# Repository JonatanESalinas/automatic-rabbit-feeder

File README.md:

# automatic-rabbit-feeder
Files to build an atomatic rabbit feeder prototype using PIC18F4550 microcontroller, a gearmotor, and a DS3231 module.

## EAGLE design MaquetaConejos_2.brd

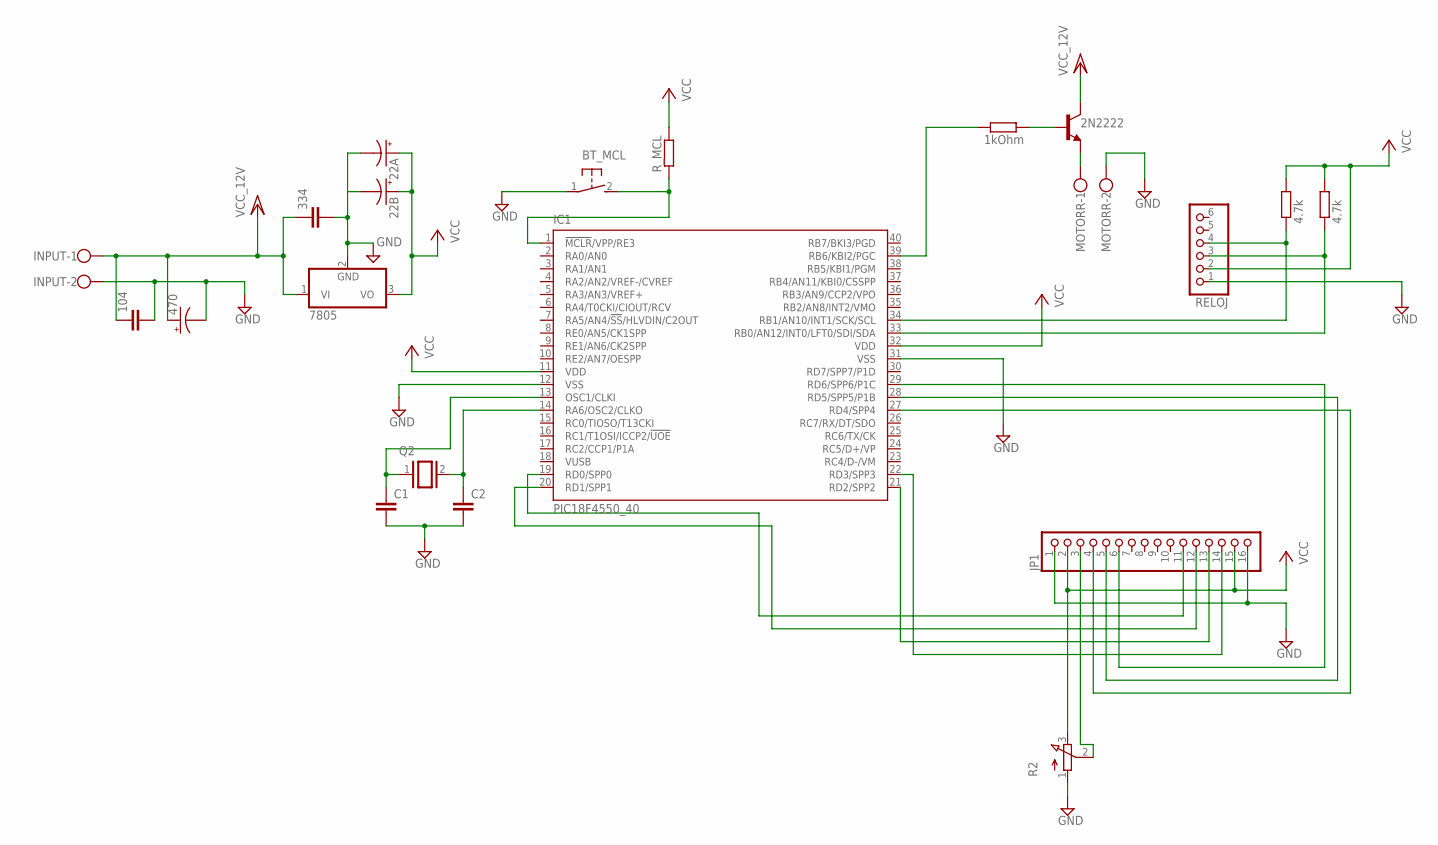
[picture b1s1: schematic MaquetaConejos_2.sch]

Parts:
22A, 22B: CPOL-USE1.8-4; E1,8-4
104, 334: C-EU050-025X075; C050-025X075
470: CPOL-USE5-10.5; E5-10,5
BT_MCL: DTS-3
C1, C2: C-EU025-024X044; C025-024X044
IC1: PIC18F4550_40; DIL40
IC3: 7805; TO220V
INPUT: W237-102
JP1: PINHD-1X16; 1X16
MOTORR: W237-102
Q2: XTAL/S; QS
R1, R4: 4.7k; 0204/7
R2: 3RP/1610N
R3: 1kOhm; 0204/7
RELOJ: PINHD-1X6; 1X06
R_MCL: R-EU_0204/7; 0204/7
T1: 2N2222; TO92-EBC-OVAL

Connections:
GND: 22A.-, 22B.-, 104.2, 334.2, 470.-, BT_MCL.1, C1.2, C2.2, IC1.12 (VSS), IC1.31 (VSS), IC3.2 (GND), INPUT.2, JP1.1, JP1.16, MOTORR.2, R2.1 (A), RELOJ.1
unnamed: BT_MCL.2, IC1.1 (!MCLR!/VPP/RE3), R_MCL.1
unnamed: IC1.39 (RB6/KBI2/PGC), R3.1
unnamed: R3.2, T1.B
unnamed: IC1.34 (RB1/AN10/INT1/SCK/SCL), R4.1, RELOJ.4
unnamed: MOTORR.1, T1.E
unnamed: C1.1, IC1.13 (OSC1/CLKI), Q2.1
unnamed: C2.1, IC1.14 (RA6/OSC2/CLKO), Q2.2
unnamed: IC1.33 (RB0/AN12/INT0/LFT0/SDI/SDA), R1.1, RELOJ.3
unnamed: JP1.3, R2.2 (S)
unnamed: IC1.19 (RD0/SPP0), JP1.11
unnamed: IC1.20 (RD1/SPP1), JP1.12
unnamed: IC1.21 (RD2/SPP2), JP1.13
unnamed: IC1.22 (RD3/SPP3), JP1.14
unnamed: IC1.27 (RD4/SPP4), JP1.4
unnamed: IC1.29 (RD6/SPP6/P1C), JP1.6
unnamed: IC1.28 (RD5/SPP5/P1B), JP1.5
VCC: 22A.+, 22B.+, IC1.11 (VDD), IC1.32 (VDD), IC3.3 (VO), JP1.2, JP1.15, R1.2, R2.3 (E), R4.2, RELOJ.2, R_MCL.2
VCC/2: 104.1, 334.1, 470.+, IC3.1 (VI), INPUT.1, T1.C

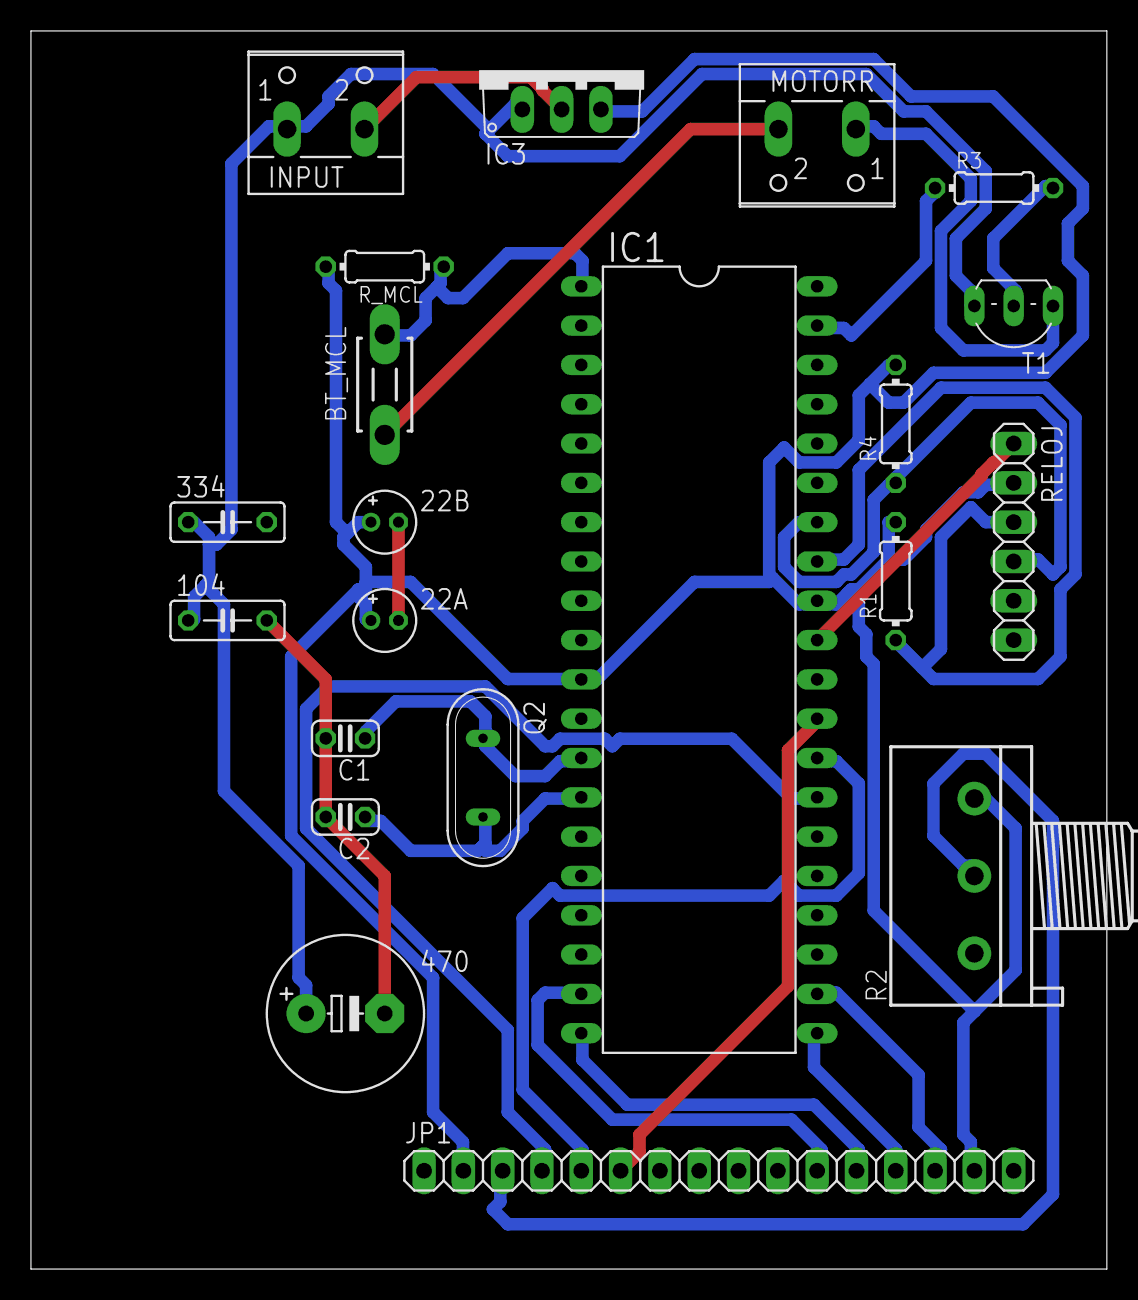
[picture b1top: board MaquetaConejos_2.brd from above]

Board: 2 copper layers, 69.5 x 80.0 mm, 21 parts (0 on the bottom side), 19 nets.

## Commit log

2019-11-11 Upload eagle schematic and board
    Eagle schematic and board to implement the circuit in a PCB.
